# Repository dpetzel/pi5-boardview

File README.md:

# Raspberry Pi 5 board reconstruction

A KiCad 10 reconstruction of the Raspberry Pi 5 board (part placement, part identification, nets traced from the
real board), published as an interactive boardview for repair work.

> [!WARNING]
> **Unofficial, incomplete and possibly wrong.**
> * **Not official.** Not made, endorsed or checked by Raspberry Pi Ltd, and not based on official schematics or layout
>   files. "Raspberry Pi" is a trademark of Raspberry Pi Ltd; this project is not affiliated with it.
> * **Made by a hobbyist.** Reverse engineered by an untrained hobbyist from photos and multimeter probing, not by an
>   electronics professional.
> * **Incomplete and possibly wrong.** Many parts are unidentified and most nets are untraced. Positions, values, part
>   numbers and connections may be wrong, and your board revision may differ.
> * **Use at your own risk.** Board-level repair can destroy hardware and can be dangerous. Check everything against
>   your own board, your own measurements and the manufacturers' datasheets before you solder or apply power. Provided
>   "as is" with no warranty of any kind; the authors and contributors accept no liability for any damage or injury.

* **View it:** <https://dpetzel.github.io/pi5-boardview/>, rebuilt from `main` on every push
* **Download:** [`pi5-boardview.html`](https://dpetzel.github.io/pi5-boardview/pi5-boardview.html) (self-contained,
  works offline) and [`pi5.brd`](https://dpetzel.github.io/pi5-boardview/pi5.brd) (for
  [OpenBoardView](https://github.com/OpenBoardView/OpenBoardView)), always the latest build

## Repository

| Path | What |
|---|---|
| `pi5.kicad_pcb`, `pi5.kicad_pro` | The board. Top and bottom photos are embedded as reference images (Eco1.User = top, Eco2.User = bottom) |
| `pi5.pretty/`, `DA9091.pretty/` | Project footprints |
| `pi5_board_top.png`, `pi5_board_bottom.png` | The source photos embedded in the board |
| `boardview.toml` | Boardview settings: title, repo link, disclaimer |
| `.github/workflows/boardview.yml` | CI: builds the boardview with [kicad-boardview](https://github.com/dpetzel/kicad-boardview) and deploys it to Pages |

The boardview files are build output and not committed.

## Contributing

Edit the board in KiCad 10 and open a pull request. Part details go in footprint fields: `Function`, `Part`, `Notes`,
`Replacement`, and `Source` (`Source2`, `Source3`, … for more links). Fields holding a URL show as links in the
viewer. References ending in `**` or `?` (`REF**`, `R?`) are shown as unidentified parts.

Every pull request builds the boardview. Download the `boardview` artifact from the PR's workflow run to check
your change before it's merged.

### Building locally

The boardview is built by [kicad-boardview](https://github.com/dpetzel/kicad-boardview), which needs KiCad's `pcbnew`
Python module. Clone it next to this repo, then with Docker:

```sh
docker run --rm -v "$PWD/..":/w -w /w/pi5-boardview kicad/kicad:10.0 python3 ../kicad-boardview/boardview.py site
```

or with the Python bundled with KiCad (on Windows, `"C:\Program Files\KiCad\10.0\bin\python.exe"`):

```sh
python3 ../kicad-boardview/boardview.py site
```

Both write `_site/`, as CI builds it: `index.html` (the viewer), `pi5-boardview.html` and `pi5.brd`. KiCad exports the
last *saved* board, so save before building. See kicad-boardview's README for the options and board conventions.

## Credits

The DA9091 PMIC footprint (`DA9091.pretty`, U5) uses the pad geometry from
[schlae/cm5-reveng](https://github.com/schlae/cm5-reveng), a reverse-engineered Raspberry Pi Compute Module 5,
licensed [CC BY-SA 4.0](https://creativecommons.org/licenses/by-sa/4.0/). Its pad numbers are left blank here on
purpose: the DA9091 has no public datasheet to confirm where pin 1 is.

## License

[CC-BY-SA-4.0](LICENSE): share and adapt with attribution, and publish adaptations under the same license.
The license's disclaimer of warranties and limitation of liability apply in full.

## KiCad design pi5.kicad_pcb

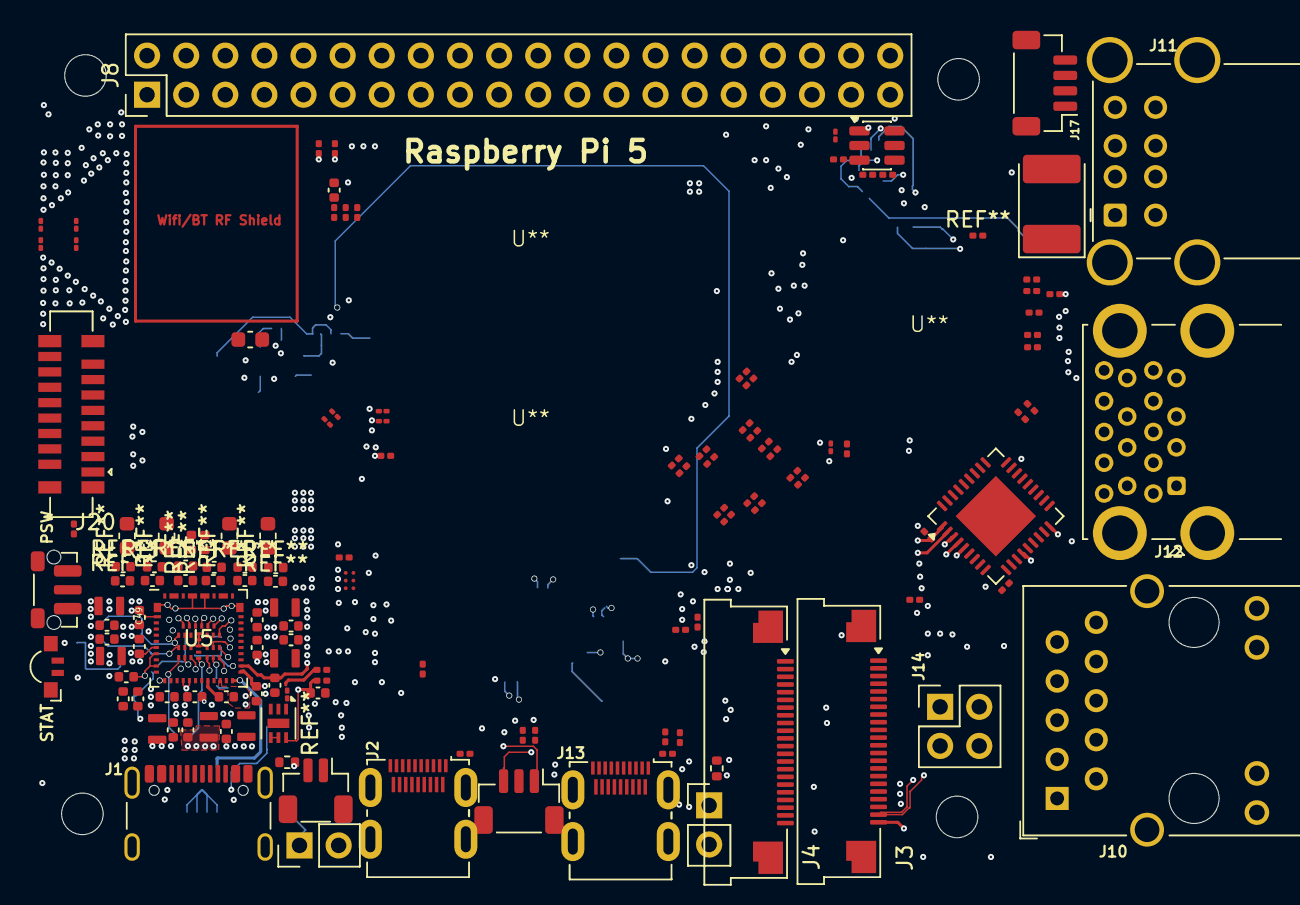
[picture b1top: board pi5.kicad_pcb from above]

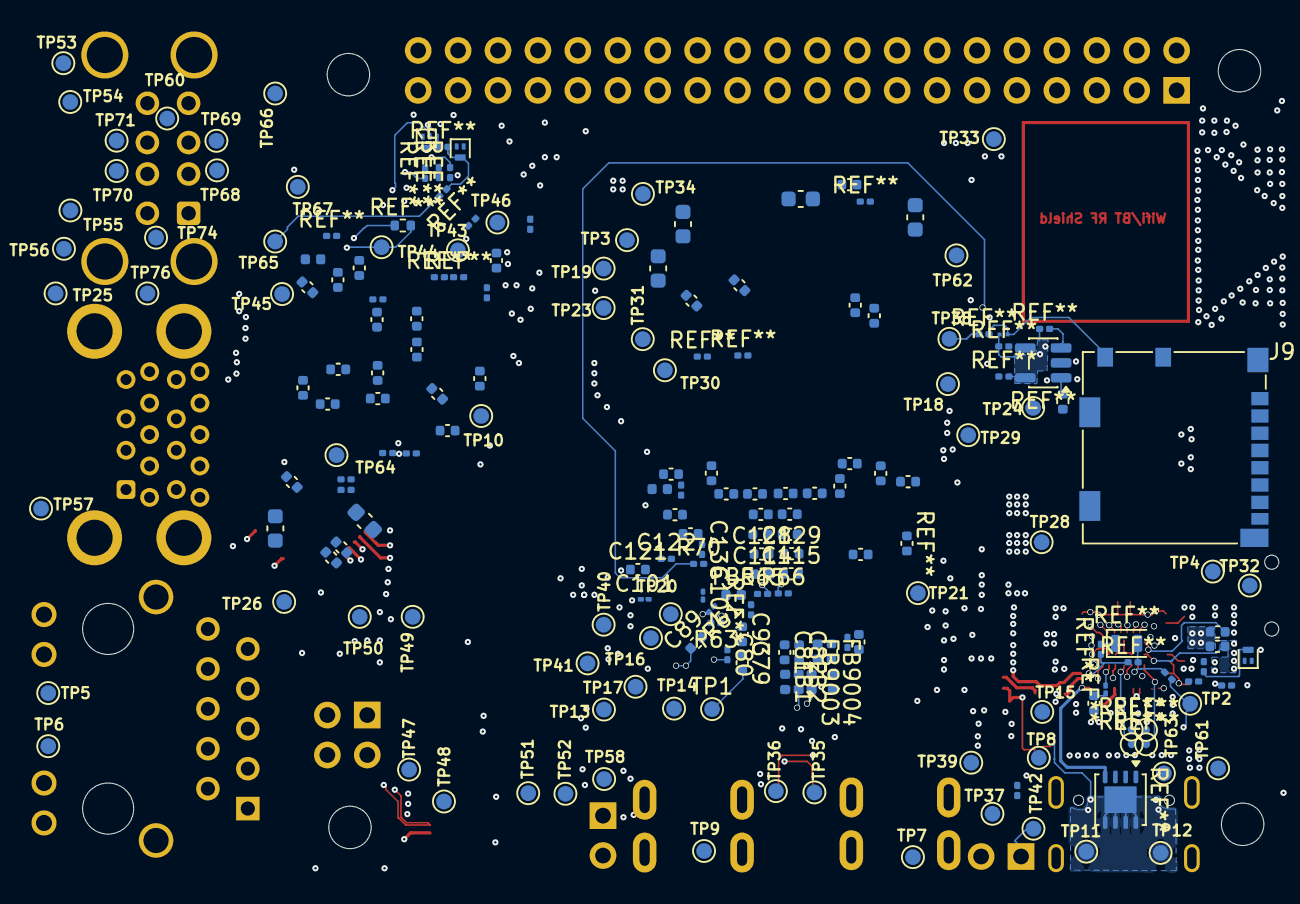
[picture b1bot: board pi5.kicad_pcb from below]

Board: 2 copper layers, 123 parts (103 on the bottom side), 11 nets.

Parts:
C49, C50: 22uF; C_0402_1005Metric
C79, C81, C82, C89, C93, C114, C115, C121, C128, C129: C; C_0402_1005Metric
C80, C122, C136: C; C_0201_0603Metric
C101, C102: C; C_01005_0402Metric
C234: 22uF; C_0603_1608Metric
C263: 4u7; C_0402_1005Metric
FB1, FB9003: 600 OHM; L_0402_1005Metric
FB2, FB9004: 220 OHM; L_0402_1005Metric
FB5: L_0402_1005Metric
J1: USB_C_Receptacle_GCT_USB4105-xx-A_16P_TopMnt_Hori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; USB_C_Receptacle_GCT_USB4105-xx-A_16P_TopMnt_Horizontal
J2, J13: HDMI_Micro-D_Molex_46765-1xxx
J3, J4: F32Q-1A7H1-11022; Amphenol_F32Q-1A7x1-11022_1x22-1MP_P0.5mm_Horizontal
J8: PinHeader_2x20_P2.54mm_Vertical
J9: 104031-0811; microSD_HC_Molex_104031-0811
J10: RJ45_Wuerth_7499111446_Horizontal
J11: USB_A_Wuerth_61400826021_Horizontal_Stacked
J12: USB3_A_Molex_48406-0001_Horizontal_Stacked
J14: PinHeader_2x02_P2.54mm_Vertical
J17: JST_SH_BM04B-SRSS-TB_1x04-1MP_P1.00mm_Vertical
J20: 52559-1652; Molex_52559-1652_2x8-1MP_P0.5mm_Vertical
PSW: SW_Push_1P1T-MP_NO_Horizontal_Alps_SKRTLAE010
R15, R17: 470 Ω; R_0201_0603Metric
R46, R47: 2K Ω; R_0201_0603Metric
R61: R; R_01005_0402Metric
R63, R65, R66, R70: R; R_0201_0603Metric
R93: 10K Ω; R_0201_0603Metric
STAT: LED_Kingbright_APFA3010_3x1.5mm_Horizontal
TP1: TestPoint; TestPoint_Pad_D1.0mm
TP2, TP3, TP4, TP5, TP6, TP7, TP8, TP9, TP10, TP11, TP12, TP13, TP14, TP15, TP16, TP17, TP18, TP19, TP20, TP21, TP23, TP24, TP25, TP26, TP28, TP29, TP30, TP31, TP32, TP33, TP34, TP35, TP36, TP37, TP38, TP39, TP40, TP41, TP42, TP43, TP44, TP45, TP46, TP47, TP48, TP49, TP50, TP51, TP52, TP53, TP54, TP55, TP56, TP57, TP58, TP60, TP61, TP62, TP63, TP64, TP65, TP66, TP67, TP68, TP69, TP70, TP71, TP74, TP76: TestPoint_Pad_D1.0mm
U5: DA9091
U**: RP1-C0
U**#2: BCM2712
U**#3: LPDDR4X_SDRAM

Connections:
+3v3: J8.1, PSW.2, U5.55
+5v: C49.2, C50.1, J8.2, J8.4, U5.1, U5.6, U5.7, U5.9, U5.12, U5.17, U5.20, U5.26, U5.27, U5.32, U5.35, U5.40, U5.66
+5v_USB-C: TP11.1, TP12.1, U5.21
GND: C49.1, C50.2, J8.6, PSW.1, U5.3, U5.4, U5.14, U5.15, U5.18, U5.29, U5.30, U5.33, U5.37, U5.38, U5.42, U5.46, U5.57, U5.58, U5.67, U5.68, U5.69, U5.70
unnamed: C79.2, TP1.TP1 (1_1)
unnamed: C81.2, FB1.1
unnamed: C82.2, FB2.1
unnamed: R61.1, R63.2
SD_SW_DETECT: J9.9, J9.10, TP38.1
VDD_1V1_RP1: U5.24, U5.60
VDD_BCM_CORE: TP28.1, U5.45

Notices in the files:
parts and their libraries:
DA9091 PMIC (QFN-71, 6x6 mm, 0.4 mm pitch). Pad geometry from U5 in schlae/cm5-reveng (https://github.com/schlae/cm5-reveng), CC BY-SA 4.0; pad numbers left blank on purpose: no public datasheet to confirm pin 1 Pad numbers applied from cm5-reveng U5 by position (2026-11-14).
